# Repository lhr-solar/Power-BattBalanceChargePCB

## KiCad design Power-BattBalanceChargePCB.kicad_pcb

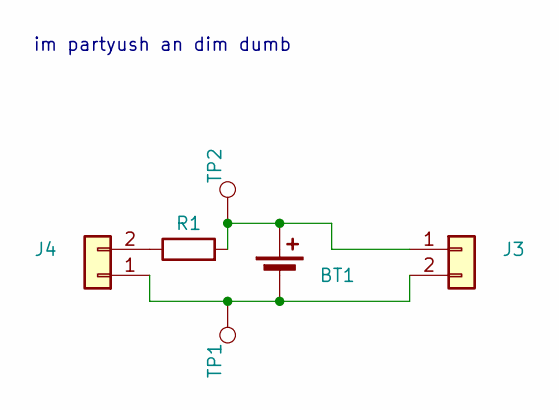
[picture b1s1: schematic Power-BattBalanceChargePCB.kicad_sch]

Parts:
BT1: Battery_Cell; 1122_with_cutout
J3: 01x02_Horizontal_Male_Pin
J4: 01x02_Horizontal_Female_Socket
R1: 1; R_0805_2012Metric
TP1, TP2: TestPoint; TestPoint_Pad_2.0x2.0mm

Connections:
unnamed: BT1.1 (+), J3.1, R1.2, TP2.1
unnamed: BT1.2 (-), J3.2, J4.1, TP1.1
unnamed: J4.2, R1.1

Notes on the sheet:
im partyush an dim dumb

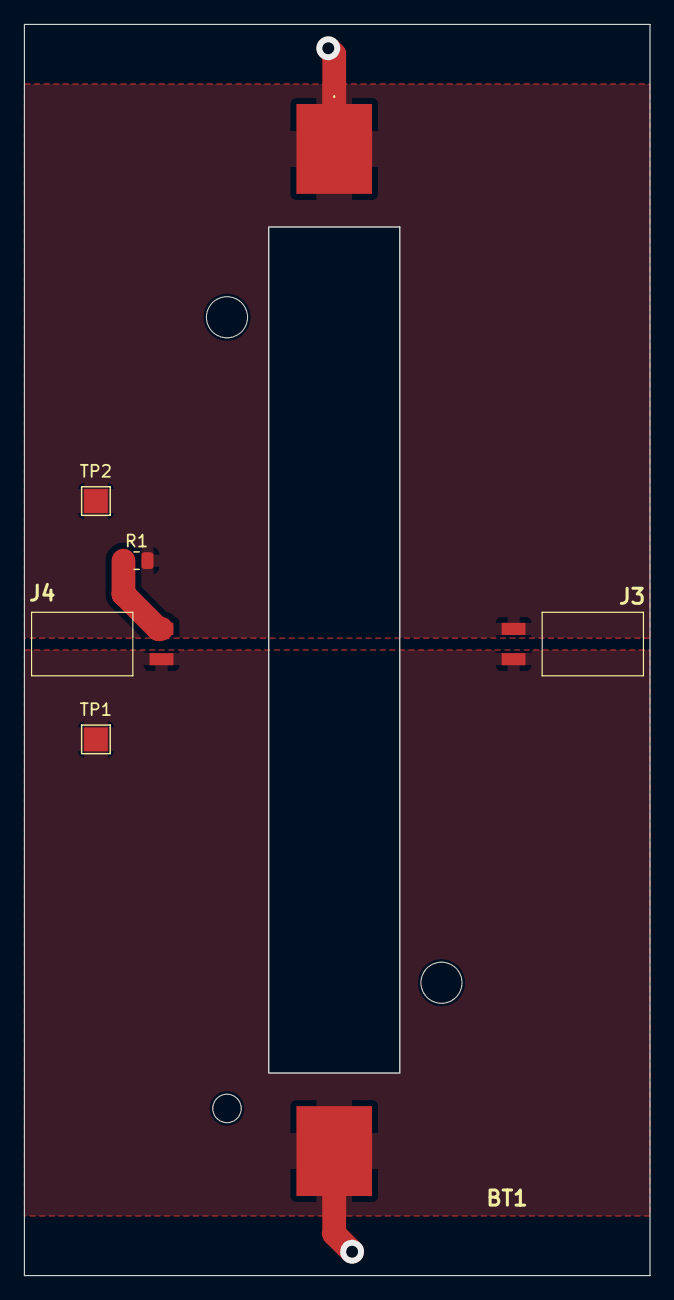
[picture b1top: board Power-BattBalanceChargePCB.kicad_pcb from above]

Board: 2 copper layers, 52.5 x 105.0 mm, 6 parts (0 on the bottom side), 3 nets.

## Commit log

2023-11-11 Version 1
2023-11-11 fixed pull request template
2023-11-11 fixed pull request template but fr this time
2023-11-11 fixing it fr fr like no cap on god
